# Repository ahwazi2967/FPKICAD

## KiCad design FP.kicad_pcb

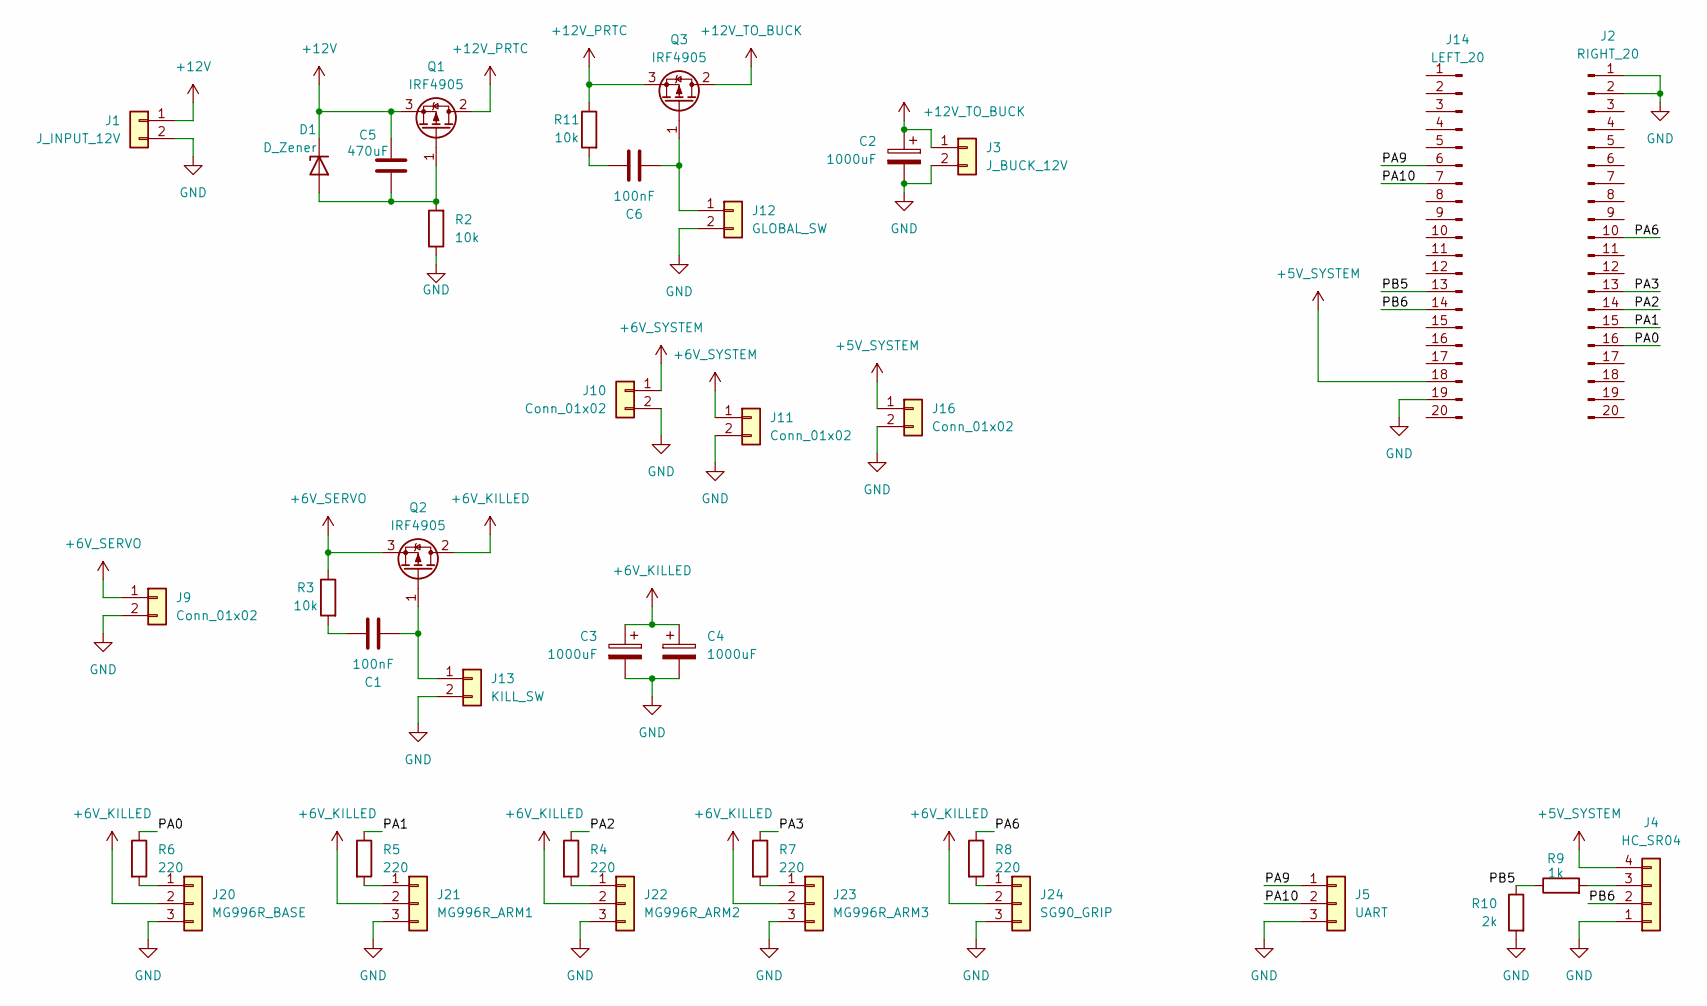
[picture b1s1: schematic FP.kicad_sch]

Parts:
C1, C6: 100nF; CP_Radial_D8.0mm_P3.50mm
C2, C3, C4: 1000uF; CP_Radial_D12.5mm_P5.00mm
C5: 470uF; CP_Radial_D8.0mm_P3.50mm
D1: D_Zener; D_DO-35_SOD27_P7.62mm_Horizontal
J1: J_INPUT_12V; HANDSON_KF301-2P
J2: RIGHT_20; PinHeader_1x20_P2.54mm_Vertical
J3: J_BUCK_12V; HANDSON_KF301-2P
J4: HC_SR04; JST_XH_B4B-XH-AM_1x04_P2.50mm_Vertical
J5: UART; JST_XH_B3B-XH-A_1x03_P2.50mm_Vertical
J9, J10: Conn_01x02; HANDSON_KF301-2P
J11, J16: Conn_01x02; PinHeader_1x02_P1.00mm_Vertical
J12: GLOBAL_SW; HANDSON_KF301-2P
J13: KILL_SW; HANDSON_KF301-2P
J14: LEFT_20; PinHeader_1x20_P2.54mm_Vertical
J20: MG996R_BASE; JST_XH_B3B-XH-A_1x03_P2.50mm_Vertical
J21: MG996R_ARM1; JST_XH_B3B-XH-A_1x03_P2.50mm_Vertical
J22: MG996R_ARM2; JST_XH_B3B-XH-A_1x03_P2.50mm_Vertical
J23: MG996R_ARM3; JST_XH_B3B-XH-A_1x03_P2.50mm_Vertical
J24: SG90_GRIP; JST_XH_B3B-XH-A_1x03_P2.50mm_Vertical
Q1, Q2, Q3: IRF4905; TO-220-3_Vertical
R2, R3, R11: 10k; R_Axial_DIN0309_L9.0mm_D3.2mm_P12.70mm_Horizontal
R4, R5, R6, R7, R8: 220; R_Axial_DIN0309_L9.0mm_D3.2mm_P12.70mm_Horizontal
R9: 1k; R_Axial_DIN0309_L9.0mm_D3.2mm_P12.70mm_Horizontal
R10: 2k; R_Axial_DIN0309_L9.0mm_D3.2mm_P12.70mm_Horizontal

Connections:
+5V_SYSTEM: J4.4, J14.18, J16.1
+6V_KILLED: C3.1, C4.1, J20.2, J21.2, J22.2, J23.2, J24.2, Q2.2 (D)
+6V_SERVO: J9.1, Q2.3 (S), R3.1
+6V_SYSTEM: J10.1, J11.1
+12V: C5.1, D1.1 (K), J1.1, Q1.3 (S)
+12V_PRTC: Q1.2 (D), Q3.3 (S), R11.1
+12V_TO_BUCK: C2.1, J3.1, Q3.2 (D)
/PA0: J2.16, R6.1
/PA1: J2.15, R5.1
/PA2: J2.14, R4.1
/PA3: J2.13, R7.1
/PA6: J2.10, R8.1
/PA9: J5.1, J14.6
/PA10: J5.2, J14.7
/PB5: J14.13, R9.1, R10.1
/PB6: J4.2, J14.14
GND: C2.2, C3.2, C4.2, J1.2, J2.1, J2.2, J3.2, J4.1, J5.3, J9.2, J10.2, J11.2, J12.2, J13.2, J14.19, J16.2, J20.3, J21.3, J22.3, J23.3, J24.3, Q2.2 (D), R2.1, R10.2
unnamed: C1.1, R3.2
unnamed: C6.1, R11.2
unnamed: C5.2, D1.2 (A), Q1.1 (G), R2.2
unnamed: J4.3, R9.2
unnamed: C6.2, J12.1, Q3.1 (G)
unnamed: C1.2, J13.1, Q2.1 (G)
unnamed: J20.1, R6.2
unnamed: J21.1, R5.2
unnamed: J22.1, R4.2
unnamed: J23.1, R7.2
unnamed: J24.1, R8.2

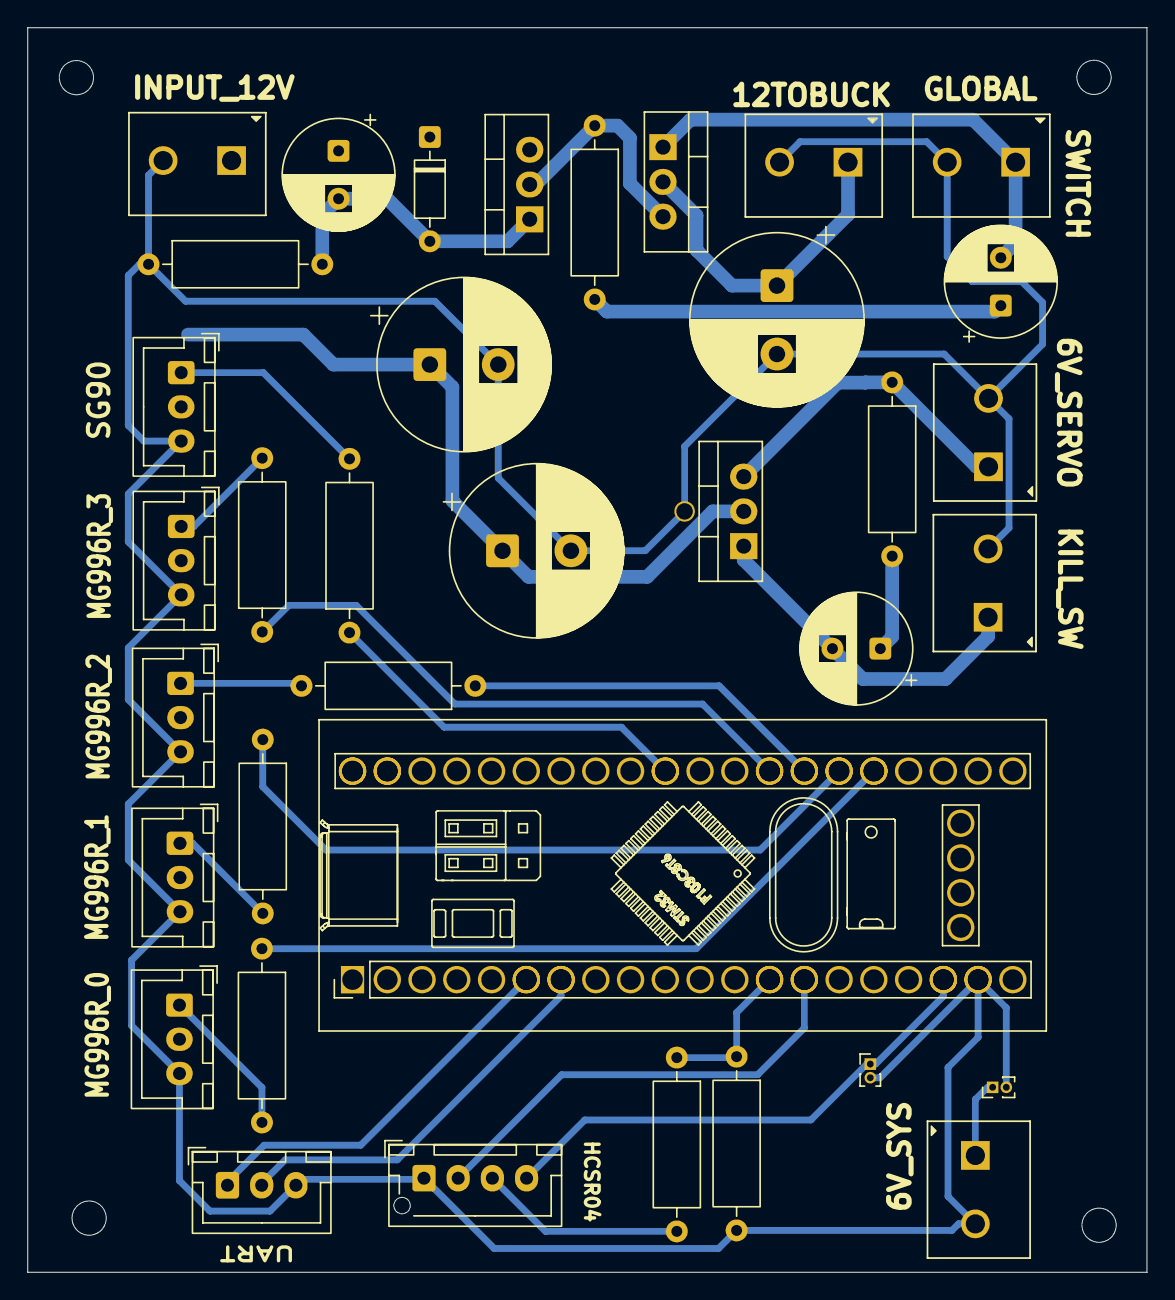
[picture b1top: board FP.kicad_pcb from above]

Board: 2 copper layers, 81.8 x 91.0 mm, 35 parts (0 on the bottom side), 20 nets.
